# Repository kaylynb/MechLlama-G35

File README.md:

# MechLlama G35
A 35 key left-handed columnar layout macropad.

## Images

## Default Layout

[Keyboard Layout Editor](http://www.keyboard-layout-editor.com/##@@_x:2&c=%238c8c8c&p=DSA%3B&=1&_x:1%3B&=3&=4&_c=%233d3d3d&t=%23ffffff%3B&=5%3B&@_y:-0.85&x:3&c=%238c8c8c&t=%23000000%3B&=2%3B&@_y:-0.65&c=%233d3d3d&t=%23ffffff%3B&=F1&_c=%238c8c8c&t=%23000000%3B&=Esc%3B&@_y:-0.5&x:2%3B&=Q&_x:1%3B&=E&=R&_c=%233d3d3d&t=%23ffffff%3B&=T%3B&@_y:-0.8500000000000001&x:3%3B&=W%3B&@_y:-0.6499999999999999%3B&=F2&_c=%238c8c8c&t=%23000000%3B&=Tab%3B&@_y:-0.5&x:2&c=%233d3d3d&t=%23ffffff%3B&=A&_x:1%3B&=D&_c=%238c8c8c&t=%23000000%3B&=F&_c=%233d3d3d&t=%23ffffff%3B&=G%3B&@_y:-0.8500000000000001&x:3%3B&=S%3B&@_y:-0.6499999999999999%3B&=F3&_c=%238c8c8c&t=%23000000%3B&=Shift%3B&@_y:-0.5&x:2%3B&=Z&_x:1%3B&=C&=V&_c=%233d3d3d&t=%23ffffff%3B&=B%3B&@_y:-0.8500000000000001&x:3&c=%238c8c8c&t=%23000000%3B&=X%3B&@_y:-0.6499999999999999&c=%233d3d3d&t=%23ffffff%3B&=F4&_c=%238c8c8c&t=%23000000%3B&=Ctrl%3B&@_y:-0.5&x:2&c=%233d3d3d&t=%23ffffff&h:1.5%3B&=Alt&_x:1&h:1.5%3B&=Enter%3B&@_y:-0.75&x:3&h:1.25%3B&=Bksp%3B&@_y:-0.75%3B&=F5&_c=%238c8c8c&t=%23000000%3B&=Super%3B&@_r:10&rx:5&ry:5.75&y:-1.75&c=%233d3d3d&t=%23ffffff&h:1.75%3B&=Space&_h:1.75%3B&=Fn)

[QMK Firmware](https://github.com/qmk/qmk_firmware/tree/master/keyboards/mechllama/g35)

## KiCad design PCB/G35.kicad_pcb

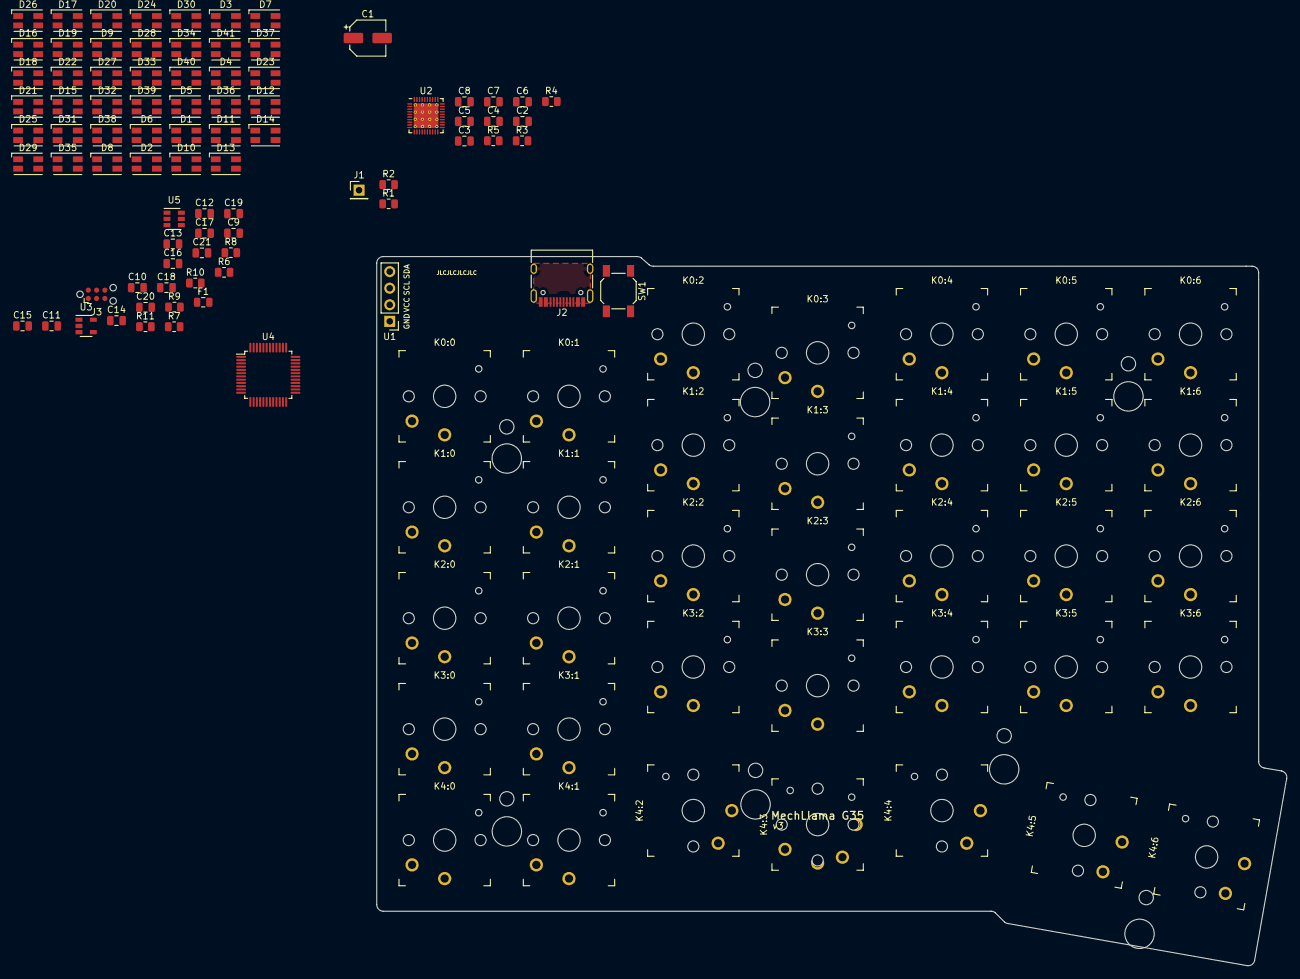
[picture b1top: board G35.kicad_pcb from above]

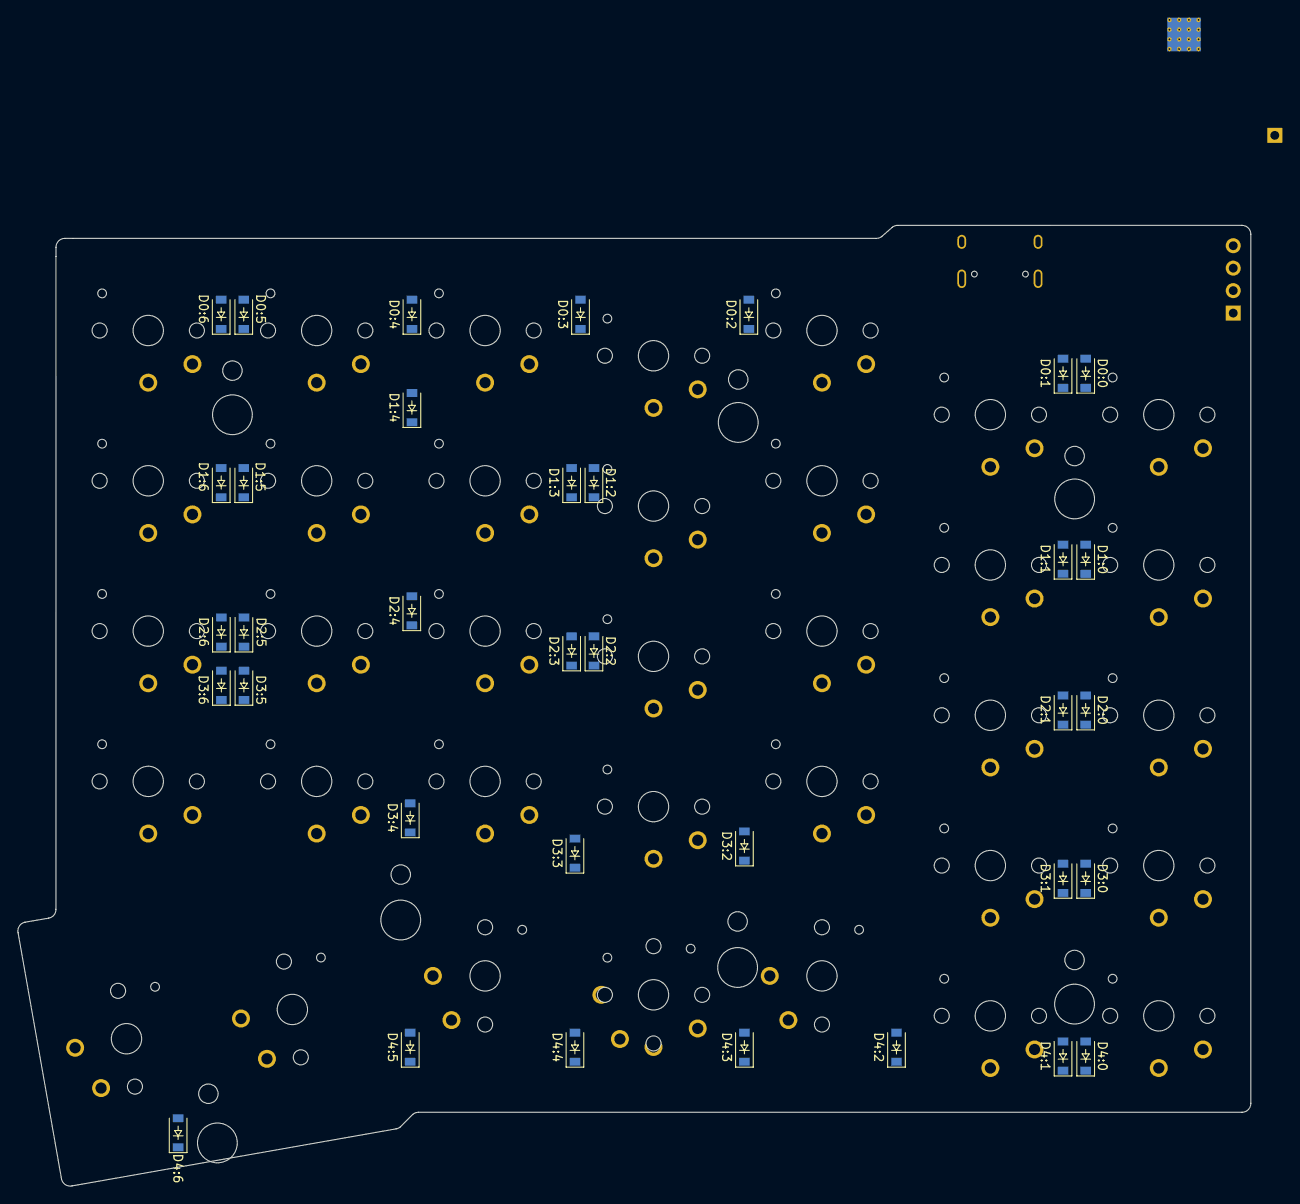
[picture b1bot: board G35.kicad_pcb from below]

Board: 2 copper layers, 139.5 x 108.7 mm, 167 parts (35 on the bottom side), 92 nets, no tracks yet.

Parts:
C1: 22uF; CP_Elec_5x3.9
C2, C3, C4, C8: 0.47uF; C_0805_2012Metric
C5, C6, C7, C10, C11, C12, C13, C17, C21: 0.1uF; C_0805_2012Metric
C9, C15, C16, C19: 1uF; C_0805_2012Metric
C14: 4.7uF; C_0805_2012Metric
C18: 0.01uF; C_0805_2012Metric
C20: 4.7nF; C_0805_2012Metric
D0:0, D0:1, D0:2, D0:3, D0:4, D0:5, D0:6, D1:0, D1:1, D1:2, D1:3, D1:4, D1:5, D1:6, D2:0, D2:1, D2:2, D2:3, D2:4, D2:5, D2:6, D3:0, D3:1, D3:2, D3:3, D3:4, D3:5, D3:6, D4:0, D4:1, D4:2, D4:3, D4:4, D4:5, D4:6: D; D_SOD-123_Nice
D1, D2, D3, D4, D5, D6, D7, D8, D9, D10, D11, D12, D13, D14, D15, D16, D17, D18, D19, D20, D21, D22, D23, D24, D25, D26, D27, D28, D29, D30, D31, D32, D33, D34, D35, D36, D37, D38, D39, D40, D41: LED_ABRG; LED_Wurth_150141M173100
F1: 500mA; Fuse_0805_2012Metric
J1: Case; PinHeader_1x01_P2.54mm_Vertical
J2: USB_C_Receptacle_USB2.0; USB_C_Receptacle_HRO_TYPE-C-31-M-12
J3: STM32_SWD; Tag-Connect_TC2030-IDC-NL_2x03_P1.27mm_Vertical
K0:0, K0:1, K0:2, K0:3, K0:4, K0:5, K0:6, K1:0, K1:1, K1:2, K1:3, K1:4, K1:5, K1:6, K2:0, K2:1, K2:2, K2:3, K2:4, K2:5, K2:6, K3:0, K3:1, K3:2, K3:3, K3:4, K3:5, K3:6, K4:0, K4:1: 1U; SW_PG1350
K4:2, K4:4, K4:5, K4:6: 1.5U; SW_PG1350_1.5u
K4:3: 1U; SW_PG1350_rotatable
M1, M2, M3, M4, M5, M6, M7: Conn_01x01; MountingHole_2.2mm_M2_DIN965
MS1, MS2, MS3, MS4, MS5, MS6, MS7: Conn_01x01; MountingHole_4.5mm_SpacerThrough
R1, R2: I2C; R_0805_2012Metric
R3, R4: 100k; R_0805_2012Metric
R5: RSET; R_0805_2012Metric
R6, R7: 5.1k; R_0805_2012Metric
R8: 1M; R_0805_2012Metric
R9: 10k; R_0805_2012Metric
R10, R11: R; R_0805_2012Metric
SW1: SW_Push; SW_SPST_SKQG_WithStem
U1: OLED_SSD1306; PinHeader_SSD1306
U2: IS31FL3737; QFN-40-1EP_5x5mm_P0.4mm_EP3.8x3.8mm_ThermalVias
U3: TLV70033_SOT23-5; SOT-23-5
U4: STM32F070CBTx; LQFP-48_7x7mm_P0.5mm
U5: USBLC6-2SC6; SOT-23-6

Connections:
+3V3: C8.1, C10.1, C11.1, C12.1, C13.1, C14.1, C16.1, C18.1, C19.1, J3.1, R1.2, R2.1, R3.2, SW1.2, U1.2, U2.32, U3.5, U4.1, U4.9, U4.24, U4.36, U4.48
+5V: C1.1, C2.1, C3.1, C4.1, C5.1, C6.1, C7.1, C15.1, C21.1, F1.1, U2.19, U2.26, U2.31, U3.1, U3.3, U5.5
/LED & OLED/RGB Matrix/CS1: D1.1, D10.1, D19.1, D28.1, U2.15
/LED & OLED/RGB Matrix/CS2: D2.1, D11.1, D20.1, D29.1, U2.16
/LED & OLED/RGB Matrix/CS3: D3.1, D12.1, D21.1, D30.1, U2.17
/LED & OLED/RGB Matrix/CS4: D4.1, D13.1, D22.1, D31.1, U2.18
/LED & OLED/RGB Matrix/CS5: D5.1, D14.1, D23.1, D32.1, U2.20
/LED & OLED/RGB Matrix/CS6: D6.1, D15.1, D24.1, D33.1, U2.21
/LED & OLED/RGB Matrix/CS7: D7.1, D16.1, D25.1, D34.1, U2.22
/LED & OLED/RGB Matrix/CS8: D8.1, D17.1, D26.1, D35.1, U2.23
/LED & OLED/RGB Matrix/CS9: D9.1, D18.1, D27.1, U2.24
/LED & OLED/RGB Matrix/CS10: D36.1, D38.1, D40.1, D41.1, U2.25
/LED & OLED/RGB Matrix/CS11: D37.1, D39.1, U2.27
/LED & OLED/RGB Matrix/SW1: D1.3, D2.3, D3.3, D4.3, D5.3, D6.3, D7.3, D8.3, D9.3, D36.3, D37.3, U2.1
/LED & OLED/RGB Matrix/SW2: D1.4, D2.4, D3.4, D4.4, D5.4, D6.4, D7.4, D8.4, D9.4, D36.4, D37.4, U2.2
/LED & OLED/RGB Matrix/SW3: D1.2, D2.2, D3.2, D4.2, D5.2, D6.2, D7.2, D8.2, D9.2, D36.2, D37.2, U2.3
/LED & OLED/RGB Matrix/SW4: D10.3, D11.3, D12.3, D13.3, D14.3, D15.3, D16.3, D17.3, D18.3, D38.3, D39.3, U2.5
/LED & OLED/RGB Matrix/SW5: D10.4, D11.4, D12.4, D13.4, D14.4, D15.4, D16.4, D17.4, D18.4, D38.4, D39.4, U2.6
/LED & OLED/RGB Matrix/SW6: D10.2, D11.2, D12.2, D13.2, D14.2, D15.2, D16.2, D17.2, D18.2, D38.2, D39.2, U2.7
/LED & OLED/RGB Matrix/SW7: D19.3, D20.3, D21.3, D22.3, D23.3, D24.3, D25.3, D26.3, D27.3, D40.3, U2.8
/LED & OLED/RGB Matrix/SW8: D19.4, D20.4, D21.4, D22.4, D23.4, D24.4, D25.4, D26.4, D27.4, D40.4, U2.9
/LED & OLED/RGB Matrix/SW9: D19.2, D20.2, D21.2, D22.2, D23.2, D24.2, D25.2, D26.2, D27.2, D40.2, U2.10
/LED & OLED/RGB Matrix/SW10: D28.3, D29.3, D30.3, D31.3, D32.3, D33.3, D34.3, D35.3, D41.3, U2.12
/LED & OLED/RGB Matrix/SW11: D28.4, D29.4, D30.4, D31.4, D32.4, D33.4, D34.4, D35.4, D41.4, U2.13
/LED & OLED/RGB Matrix/SW12: D28.2, D29.2, D30.2, D31.2, D32.2, D33.2, D34.2, D35.2, D41.2, U2.14
/LED & OLED/SCL: R1.1, U1.3, U2.35, U4.45
/LED & OLED/SDA: R2.2, U1.4, U2.34, U4.46
/MCU, USB, & Power/BOOT0: R9.1, SW1.1, U4.44
/MCU, USB, & Power/D+: R11.2, U4.30
/MCU, USB, & Power/D-: R10.2, U4.29
/MCU, USB, & Power/DR+: J2.A6, J2.B6, U5.3
/MCU, USB, & Power/DR-: J2.A7, J2.B7, U5.1
/MCU, USB, & Power/NRST: C17.1, J3.3, U4.7
/MCU, USB, & Power/SHIELD: C20.1, J1.1, J2.S1, R8.1
/MCU, USB, & Power/SWCLK: J3.4, U4.32
/MCU, USB, & Power/SWDIO: J3.2, U4.31
GND: C1.2, C2.2, C3.2, C4.2, C5.2, C6.2, C7.2, C8.2, C9.2, C10.2, C11.2, C12.2, C13.2, C14.2, C15.2, C16.2, C17.2, C18.2, C19.2, C20.2, C21.2, J2.A1, J2.A12, J2.B1, J2.B12, J3.5, R4.2, R5.2, R6.2, R7.1, R8.2, R9.2, U1.1, U2.4, U2.11, U2.29, U2.36, U2.40, U2.41, U3.2, U4.8, U4.23, U4.35, U4.47, U5.2
unnamed: D0:0.2, K0:0.2
unnamed: D0:1.2, K0:1.2
unnamed: D0:2.2, K0:2.2
unnamed: D0:3.2, K0:3.2
unnamed: D0:4.2, K0:4.2
unnamed: D0:5.2, K0:5.2
unnamed: D0:6.2, K0:6.2
unnamed: D1:0.2, K1:0.2
unnamed: D1:1.2, K1:1.2
unnamed: D1:2.2, K1:2.2
unnamed: D1:3.2, K1:3.2
unnamed: D1:4.2, K1:4.2
unnamed: D1:5.2, K1:5.2
unnamed: D1:6.2, K1:6.2
unnamed: D2:0.2, K2:0.2
unnamed: D2:1.2, K2:1.2
unnamed: D2:2.2, K2:2.2
unnamed: D2:3.2, K2:3.2
unnamed: D2:4.2, K2:4.2
unnamed: D2:5.2, K2:5.2
unnamed: D2:6.2, K2:6.2
unnamed: D3:0.2, K3:0.2
unnamed: D3:1.2, K3:1.2
unnamed: D3:2.2, K3:2.2
unnamed: D3:3.2, K3:3.2
unnamed: D3:4.2, K3:4.2
unnamed: D3:5.2, K3:5.2
unnamed: D3:6.2, K3:6.2
unnamed: D4:0.2, K4:0.2
unnamed: D4:1.2, K4:1.2
unnamed: D4:2.2, K4:2.2
unnamed: D4:3.2, K4:3.2
unnamed: D4:4.2, K4:4.2
unnamed: D4:5.2, K4:5.2
unnamed: D4:6.2, K4:6.2
unnamed: J2.A5, R6.1
unnamed: J2.B5, R7.2
unnamed: R3.1, U2.38
unnamed: R4.1, U2.39
unnamed: R5.1, U2.30
unnamed: R10.1, U5.6
unnamed: R11.1, U5.4
VBUS: C9.1, F1.2, J2.A4, J2.A9, J2.B4, J2.B9
col0: K0:0.1, K1:0.1, K2:0.1, K3:0.1, K4:0.1
col1: K0:1.1, K1:1.1, K2:1.1, K3:1.1, K4:1.1
col2: K0:2.1, K1:2.1, K2:2.1, K3:2.1, K4:2.1
col3: K0:3.1, K1:3.1, K2:3.1, K3:3.1, K4:3.1
col4: K0:4.1, K1:4.1, K2:4.1, K3:4.1, K4:4.1
col5: K0:5.1, K1:5.1, K2:5.1, K3:5.1, K4:5.1
col6: K0:6.1, K1:6.1, K2:6.1, K3:6.1, K4:6.1
row0: D0:0.1, D0:1.1, D0:2.1, D0:3.1, D0:4.1, D0:5.1, D0:6.1
row1: D1:0.1, D1:1.1, D1:2.1, D1:3.1, D1:4.1, D1:5.1, D1:6.1
row2: D2:0.1, D2:1.1, D2:2.1, D2:3.1, D2:4.1, D2:5.1, D2:6.1
row3: D3:0.1, D3:1.1, D3:2.1, D3:3.1, D3:4.1, D3:5.1, D3:6.1
row4: D4:0.1, D4:1.1, D4:2.1, D4:3.1, D4:4.1, D4:5.1, D4:6.1

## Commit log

2019-07-03 Import from old repository
2019-07-03 Add MIT license
2019-07-04 Add layout image to readme
2019-07-04 Add higher quality layout image
2019-07-05 Add images to readme
2019-07-05 Fixup readme
2019-07-05 Initial cleanup fixes
    Remove extra thumb key footprint
    Cleanup widths of main GND and +5V traces
    Combine ground zone for crystal and mcu
    Move 1x6 ISP header closer to mcu
2019-07-07 Update MX_Alps_Hybrid
2020-03-08 Add link to qmk firmware in README
2020-12-02 Initial work on arm conversion
2021-03-26 stage
2021-03-26 update edge cuts
